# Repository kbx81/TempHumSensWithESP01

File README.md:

# kbx's Temperature and Humidity Sensor Board for ESP-01

## What?

Just another environmental sensor board to plug an ESP-01 module onto.
 It was designed with [ESPHome](https://esphome.io) in mind but should work fine
 with [Tasmota](https://tasmota.github.io/docs/) or any other app, really.

## Why?

I needed a sensor board to monitor the humidity in my filament storage box.
 I was somewhat unhappy with the tiny DHT22 boards that are typically available
 on Amazon and elsewhere so I spun my own version. The dual-sensor arrangement
 allows for some redundancy -- they, in a sense, verify each other to help
 increase confidence in the readings/data they provide.

The board itself is sized to align with extra mounting holes that seem to be
 in the Prusa MK3 frame. With the help of the [spacer](BME280+SHTC3BoardMountForPrusaMK3.stl)
 I drew up, it should be possible to mount it directly to the printer's frame
 with just two M3 screws from your "spare parts" baggy. I've done this to monitor
 the temperature inside of the LACK enclosure I built for my printer with the help
 of [Home Assistant](https://www.home-assistant.io), [ESPHome](https://esphome.io)
 and [Grafana](https://grafana.com). This board can be powered from a spare 5-volt
 header that's near the top of the MK3's RAMbo board (the cable is visible in the
 pictures I've placed into the [images](images/) directory).

## How?

Please see the BoM [here](TempHumSensWithESP01.bom.csv) or
 [here](https://octopart.com/bom-tool/L01oa2CK) for a list of parts needed to
 build one. I had the PCBs fabricated by [Elecrow](https://www.elecrow.com) but
 nearly any PCB fabricator should be able to manufacture these without any issues.

The schematic and PCB were drawn in [KiCAD](https://www.kicad-pcb.org).

The BME280 is the most challenging part on this board -- the pads are on the
 underside of the device. You'll need a steady hand and either a hot air station
 or a reflow oven to solder this part to the board. The rest of the components are
 pretty easy to work with.

Note that `R7` is optional; you can use it as a pull-up resistor in the event that
 you'd like to connect a DHTxx module to the RX/GPIO3 line on the ESP-01. Why?
 Because more sensors...duh...

 ## Legal stuff and License

The circuit schematics and PCB found here are licensed under the
 [Creative Commons Attribution-ShareAlike 4.0 International License](http://creativecommons.org/licenses/by-sa/4.0/).

_Happy building!_

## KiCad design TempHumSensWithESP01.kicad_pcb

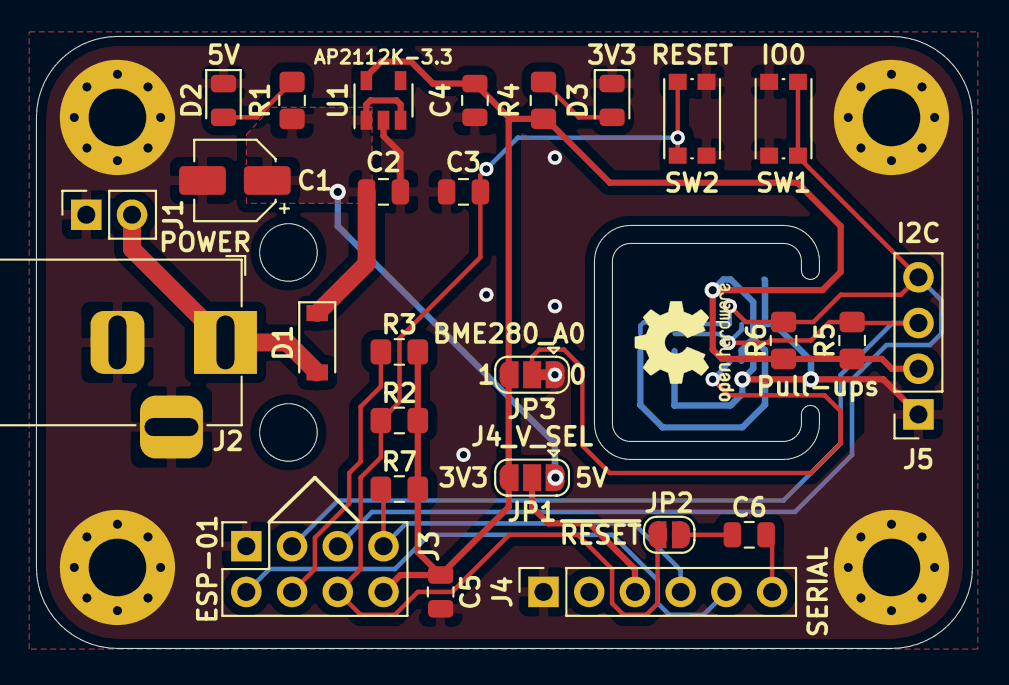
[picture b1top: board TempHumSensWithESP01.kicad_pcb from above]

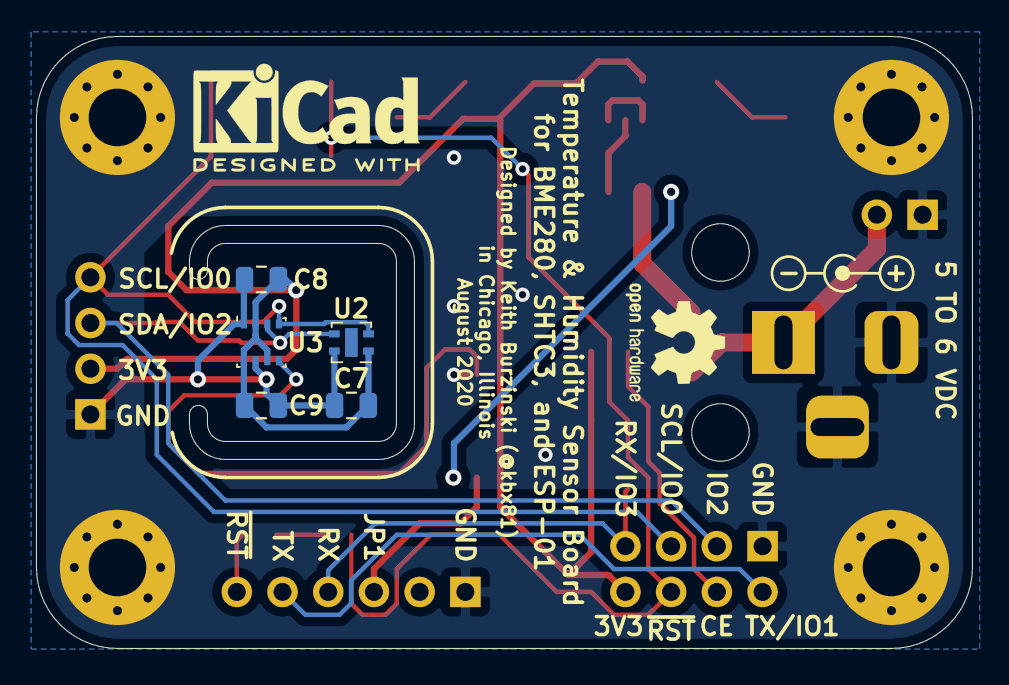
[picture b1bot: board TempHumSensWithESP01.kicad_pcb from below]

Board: 2 copper layers, 52.0 x 34.0 mm, 38 parts (7 on the bottom side), 16 nets.

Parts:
C1: 10 uF; CP_Elec_4x5.8
C2, C4: 1 uF; C_0805_2012Metric
C3, C6, C7, C8, C9: 100 nF; C_0805_2012Metric
C5: 10 uF; C_0805_2012Metric
D1: MBR120; D_SOD-123
D2: 5V; LED_0805_2012Metric
D3: 3V3; LED_0805_2012Metric
H1, H2, H3, H4: MountingHole_Pad; MountingHole_3.2mm_M3_Pad_Via
H5, H6: MountingHole; MountingHole_3.2mm_M3
J1: POWER; PinSocket_1x02_P2.54mm_Vertical
J2: 5 TO 6 VDC; BarrelJack_Horizontal
J3: ESP-01; PinSocket_2x04_P2.54mm_Vertical
J4: SERIAL; PinSocket_1x06_P2.54mm_Vertical
J5: I2C; PinSocket_1x04_P2.54mm_Vertical
JP1: J4_V_SEL; SolderJumper-3_P1.3mm_Open_RoundedPad1.0x1.5mm
JP2: ~RESET; SolderJumper-2_P1.3mm_Open_RoundedPad1.0x1.5mm
JP3: BME280_A0; SolderJumper-3_P1.3mm_Bridged12_RoundedPad1.0x1.5mm
R1: 8K2; R_0805_2012Metric_Pad1.15x1.40mm_HandSolder
R2, R3, R7: 10K; R_0805_2012Metric_Pad1.15x1.40mm_HandSolder
R4: 1K6; R_0805_2012Metric_Pad1.15x1.40mm_HandSolder
R5, R6: 3K3; R_0805_2012Metric_Pad1.15x1.40mm_HandSolder
SW1: IO0; SW_Push_1P1T_NO_CK_KMR2
SW2: RESET; SW_Push_1P1T_NO_CK_KMR2
U1: AP2112K-3.3; SOT-23-5
U2: SHTC3; AMS_QFN-4-1EP_2x2mm_P0.95mm_EP0.7x1.6mm
U3: BME280; Bosch_LGA-8_2.5x2.5mm_P0.65mm_ClockwisePinNumbering

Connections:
+3V3: C4.1, C5.1, C7.1, C8.1, C9.1, J3.8, J5.2, JP1.3, JP3.3, R2.2, R3.2, R4.1, R5.1, R6.1, R7.2, U1.5, U2.1, U3.2, U3.6, U3.8
+5V: C1.1, C2.1, D1.1, JP1.1, R1.1, U1.1, U1.3
/ESP_CH_EN: J3.4, R3.1
/ESP_GPIO0_SCL: J3.5, J5.4, R6.2, SW1.1, U2.2, U3.4
/ESP_GPIO1_TX: J3.2, J4.5
/ESP_GPIO2_SDA: J3.3, J5.3, R5.2, U2.3, U3.3
/ESP_GPIO3_RX: J3.7, J4.4, R7.1
/~ESP_RESET: C3.1, J3.6, JP2.2, R2.1, SW2.1
GND: C1.2, C2.2, C3.2, C4.2, C5.2, C7.2, C8.2, C9.2, D2.1, D3.1, H1.1, H2.1, H3.1, H4.1, J1.1, J2.2, J2.3, J3.1, J4.1, J5.1, JP3.1, SW1.2, SW2.2, U1.2, U2.4, U3.1, U3.7
unnamed: C6.1, JP2.1
unnamed: C6.2, J4.6
unnamed: D1.2, J1.2, J2.1
unnamed: D2.2, R1.2
unnamed: D3.2, R4.2
unnamed: J4.3, JP1.2
unnamed: JP3.2, U3.5

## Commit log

2020-11-11 Add MK3 mount
2020-11-11 Copy
2020-11-11 Copy, gerbers

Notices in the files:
README.md:
Creative Commons License badge
